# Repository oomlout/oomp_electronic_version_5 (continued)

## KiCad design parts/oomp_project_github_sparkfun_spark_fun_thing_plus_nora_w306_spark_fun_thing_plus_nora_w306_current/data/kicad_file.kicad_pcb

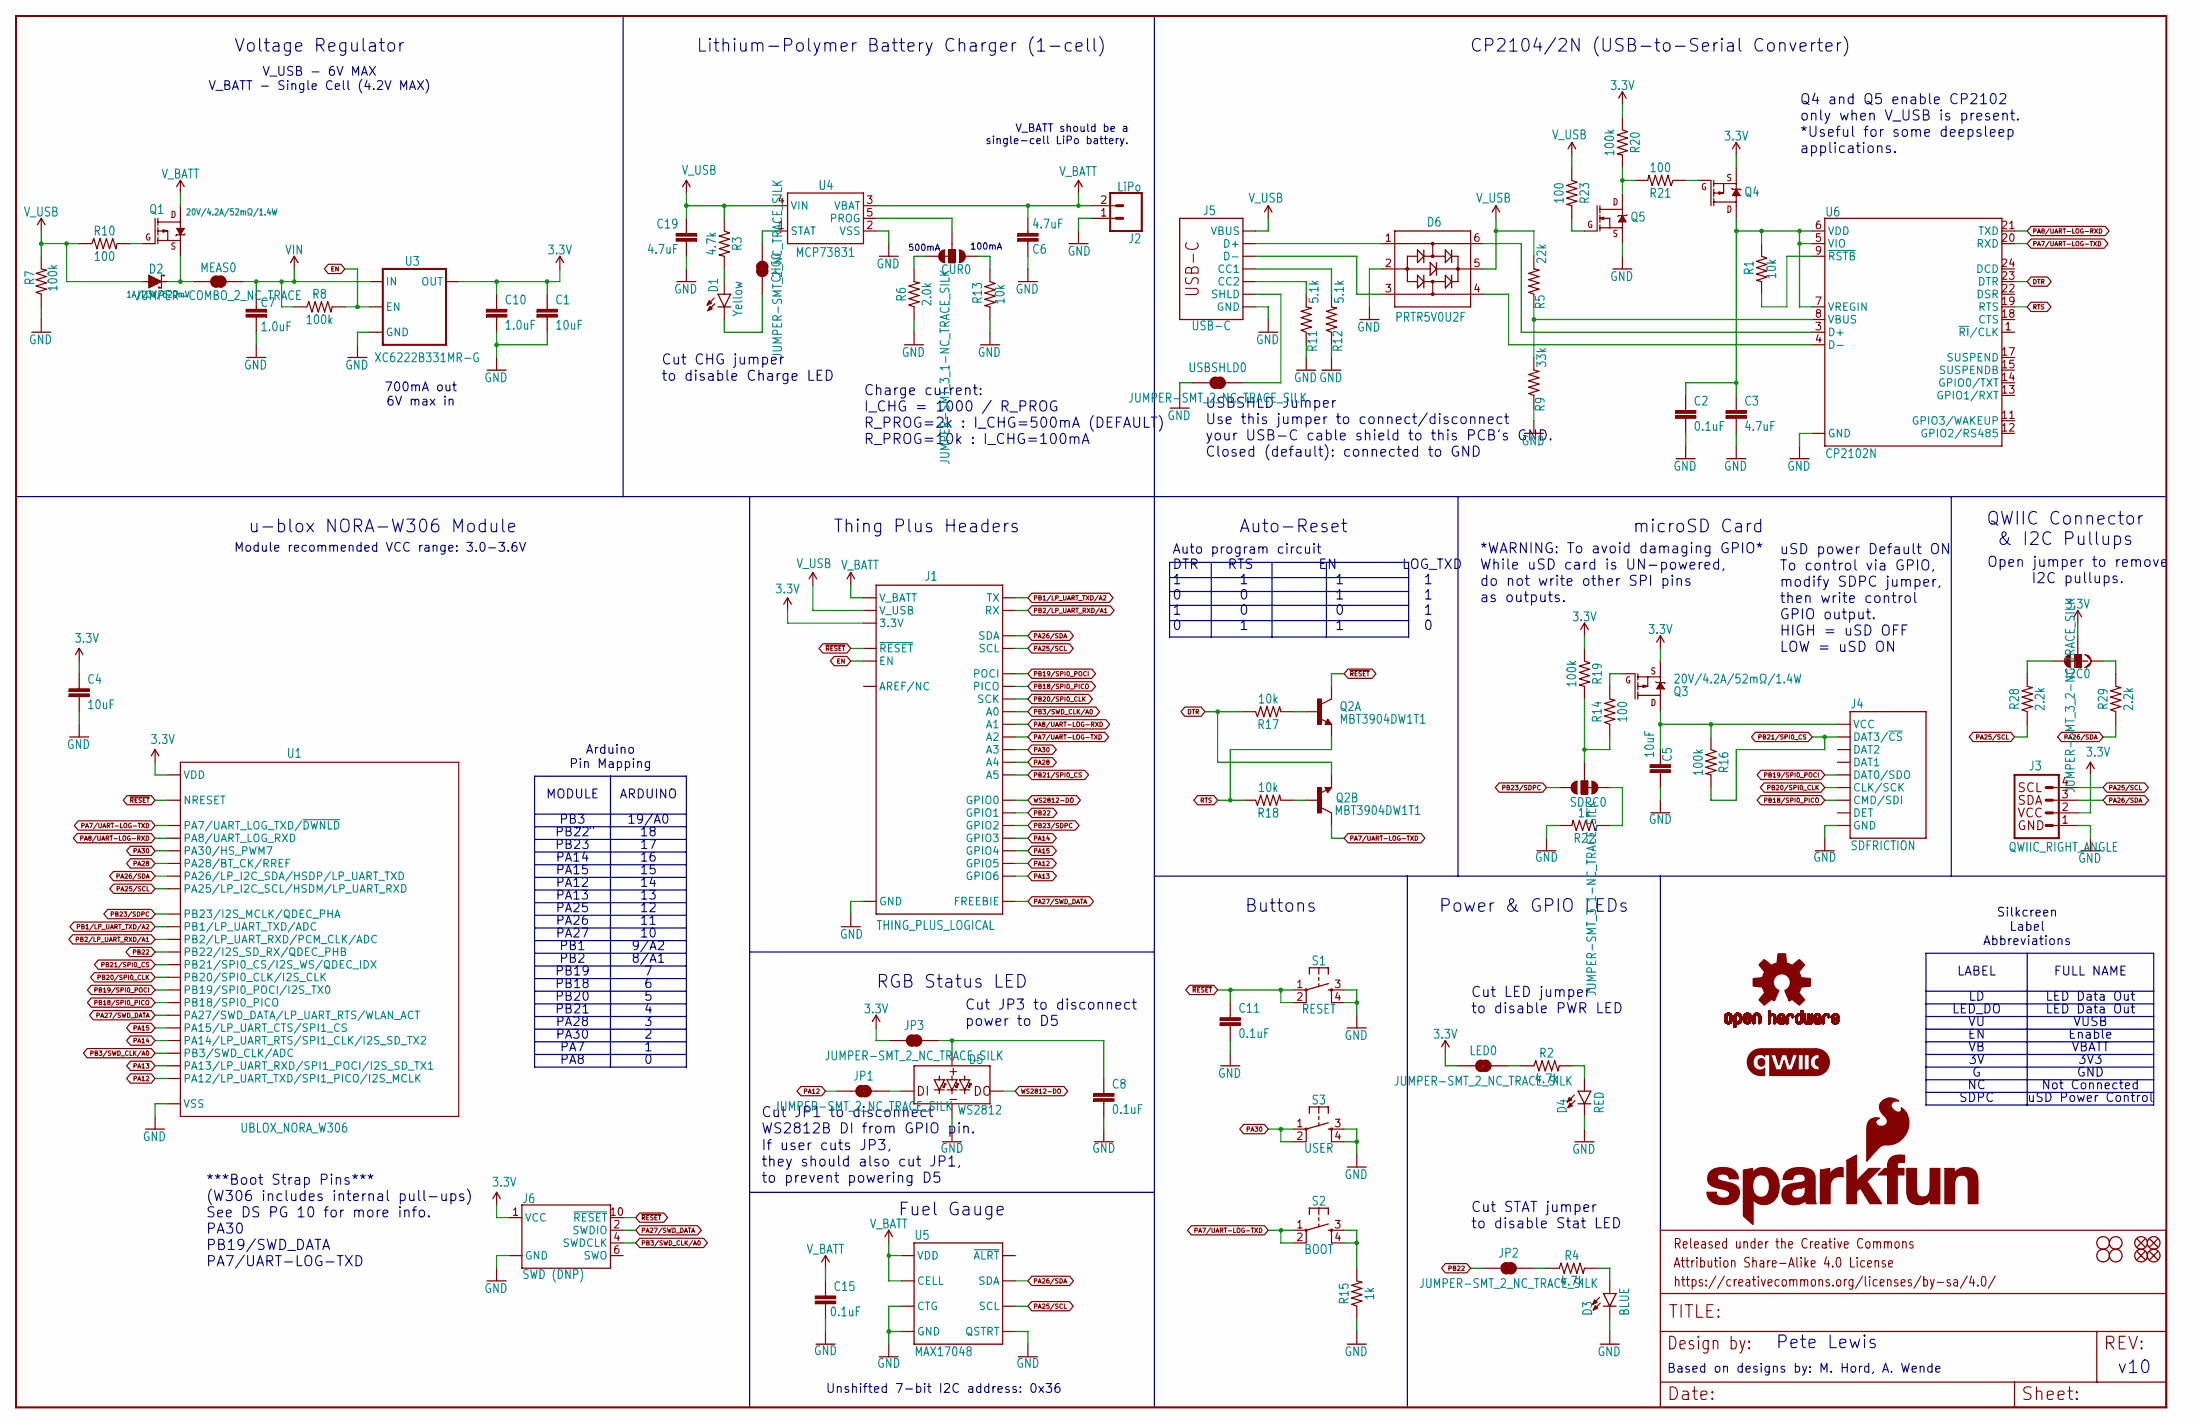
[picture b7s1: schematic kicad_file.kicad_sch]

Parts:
C1, C4, C5: 10uF; 0402-TIGHT
C2, C8, C11, C15: 0.1uF; 0402-TIGHT
C3, C6, C19: 4.7uF; 0603
C7, C10: 1.0uF; 0402-TIGHT
CHG0: JUMPER-SMT_2_NC_TRACE_SILK; SMT-JUMPER_2_NC_TRACE_SILK
CUR0: JUMPER-SMT_3_1-NC_TRACE_SILK; SMT-JUMPER_3_1-NC_TRACE_SILK
D1: Yellow; LED-0603
D2: 1A/23V/620mV; SOD-323
D3: BLUE; LED-0603
D4: RED; LED-0603
D5: WS2812; WS2812-2020
D6: PRTR5V0U2F; SOT886
FD1, FD2, FD3, FD4: FIDUCIALUFIDUCIAL; FIDUCIAL-MICRO
FRAME1: FRAME-LEDGER; CREATIVE_COMMONS
H1, H2, H3, H4: STAND-OFF
I2C0: JUMPER-SMT_3_2-NC_TRACE_SILK; SMT-JUMPER_3_2-NC_TRACE_SILK
J1: THING_PLUS_LOGICAL; THING_PLUS
J2: LiPo; JST-2-SMD
J3: QWIIC_RIGHT_ANGLE; JST04_1MM_RA
J4: SDFRICTION; MICROSD_TINY
J5: USB-C; USB-C-16P-4LAYER-ISOLATED
J6: SWD (DNP); 2X5-SMD-UNSHROUDED_DNP_NO_PASTE
JP1, JP2, JP3: JUMPER-SMT_2_NC_TRACE_SILK; SMT-JUMPER_2_NC_TRACE_SILK
LED0: JUMPER-SMT_2_NC_TRACE_SILK; SMT-JUMPER_2_NC_TRACE_SILK
LOGO2: OSHW-LOGOM; OSHW-LOGO-M
LOGO3: SFE_LOGO_NAME_FLAME.1_INCH; SFE_LOGO_NAME_FLAME_.1
LOGO6: QWIIC_LOGO_4MM; QWIIC_4MM
MEAS0: JUMPER-COMBO_2_NC_TRACE; COMBO-JUMPER_2_NC_TRACE
Q1, Q3, Q4: 20V/4.2A/52mΩ/1.4W; SOT23-3
Q2: MBT3904DW1T1; SC70-6
Q5: 20V/0.2A/8MHz/1.2Ω/1Vth; SOT-416FL
R1, R13, R17, R18: 10k; 0402-TIGHT
R2, R3, R4: 4.7k; 0402-TIGHT
R5: 22k; 0402-TIGHT
R6: 2.0k; 0603
R7, R8, R16, R19, R20: 100k; 0402-TIGHT
R9: 33k; 0402-TIGHT
R10, R14, R21, R23: 100; 0402-TIGHT
R11, R12: 5.1k; 0402-TIGHT
R15, R22: 1k; 0402-TIGHT
R28, R29: 2.2k; 0402-TIGHT
S1: RESET; TACTILE_SWITCH_SMD_4.6X2.8MM
S2: BOOT; TACTILE_SWITCH_SMD_4.6X2.8MM
S3: USER; TACTILE_SWITCH_SMD_4.6X2.8MM
SDPC0: JUMPER-SMT_3_1-NC_TRACE_SILK; SMT-JUMPER_3_1-NC_TRACE_SILK
U1: UBLOX_NORA_W306; UBLOX-NORA-W3
U3: XC6222B331MR-G; SOT23-5
U4: MCP73831; SOT23-5
U5: MAX17048; DFN-8
U6: CP2102N; QFN24
USBSHLD0: JUMPER-SMT_2_NC_TRACE_SILK; SMT-JUMPER_2_NC_TRACE_SILK

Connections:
3.3V: C1.1, C4.1, C10.1, I2C0.2, J1.27 (3.3V), J3.2, J6.1 (VCC), JP3.1, LED0.1, Q3.2 (S), Q4.2 (S), R19.1, R20.1, U1.A7 (VDD), U1.A8 (VDD), U1.B7 (VDD), U3.5 (OUT)
CC1: J5.A5 (CC1), R12.2
CC2: J5.B5 (CC2), R11.2
CHG: CHG0.2, U4.1 (STAT)
DTR: Q2.1 (E), R17.1, U6.23 (DTR)
EN: J1.11 (EN), R8.2, U3.3 (EN)
GND: C1.2, C2.2, C3.2, C4.2, C5.2, C6.2, C7.2, C8.2, C10.2, C11.2, C15.2, C19.2, D3.C, D4.C, D5.GND, D6.2, J1.25 (GND), J2.1 (2), J3.1, J4.6 (GND), J4.GND1 (GND), J4.GND2 (GND), J4.GND3 (GND), J4.GND4 (GND), J4.GND5 (GND), J4.GND6 (GND), J5.GND, J5.GND2 (GND), J6.3 (GND), J6.5 (GND), J6.9 (GND), Q5.2 (S), R6.1, R7.1, R9.1, R11.1, R12.1, R13.2, R15.1, R22.2, S1.3, S1.4, S3.3, S3.4, U1.A1 (VSS), U1.A9 (VSS), U1.B2 (VSS), U1.B8 (VSS), U1.E4 (VSS), U1.E5 (VSS), U1.F4 (VSS), U1.F5 (VSS), U1.K2 (VSS), U1.K3 (VSS), U1.K5 (VSS), U1.K7 (VSS), U1.K8 (VSS), U1.L1 (VSS), U1.L9 (VSS), U1.M1 (VSS), U1.M2 (VSS), U1.M8 (VSS), U1.M9 (VSS), U3.2 (GND), U4.2 (VSS), U5.1 (CTG), U5.4 (GND), U5.6 (QSTRT), U5.9 (GND), U6.2 (GND), U6.PAD (GND), USBSHLD0.1
unnamed: R1.2, U6.9 (~RSTB)
unnamed: D3.A, R4.2
unnamed: Q2.5 (B), R17.2
unnamed: R5.1, R9.2, U6.8 (VBUS)
unnamed: Q2.2 (B), R18.2
unnamed: CHG0.1, D1.C
unnamed: Q1.1 (G), R10.2
unnamed: R15.2, S2.3, S2.4
unnamed: CUR0.2, U4.5 (PROG)
unnamed: D5.DI, JP1.2
unnamed: CUR0.1, R13.1
unnamed: LED0.2, R2.1
unnamed: CUR0.3, R6.2
unnamed: D4.A, R2.2
unnamed: D6.6, U6.3 (D+)
unnamed: D6.1, J5.A6 (D+), J5.B6 (D+)
unnamed: D1.A, R3.2
unnamed: D6.4, U6.4 (D-)
unnamed: D6.3, J5.A7 (D-), J5.B7 (D-)
unnamed: I2C0.3, R28.2
unnamed: I2C0.1, R29.2
unnamed: JP2.2, R4.1
unnamed: D2.C, MEAS0.1, MEAS0.3 (1), Q1.2 (S)
unnamed: Q3.1 (G), R14.2
unnamed: C5.1, J4.4 (VCC), Q3.3 (D), R16.1
unnamed: R14.1, R19.2, SDPC0.2
unnamed: Q5.3 (D), R20.2, R21.2
unnamed: C8.1, D5.VCC, JP3.2
unnamed: C2.1, C3.1, Q4.3 (D), R1.1, U6.5 (VIO), U6.6 (VDD), U6.7 (VREGIN)
unnamed: Q4.1 (G), R21.1
unnamed: Q5.1 (G), R23.2
unnamed: R22.1, SDPC0.3
PA7/UART-LOG-TXD: J1.22 (A2), Q2.6 (C), S2.1, S2.2, U1.A5 (PA7/UART_LOG_TXD/~DWNLD), U6.20 (RXD)
PA8/UART-LOG-RXD: J1.23 (A1), U1.A6 (PA8/UART_LOG_RXD), U6.21 (TXD)
PA12: J1.4 (GPIO5), JP1.1, U1.J9 (PA12/LP_UART_TXD/SPI1_PICO/I2S_MCLK)
PA13: J1.3 (GPIO6), U1.J8 (PA13/LP_UART_RXD/SPI1_POCI/I2S_SD_TX1)
PA14: J1.6 (GPIO3), U1.H9 (PA14/LP_UART_RTS/SPI1_CLK/I2S_SD_TX2)
PA15: J1.5 (GPIO4), U1.H8 (PA15/LP_UART_CTS/SPI1_CS)
PA25/SCL: J1.2 (SCL), J3.4, R28.1, U1.C2 (PA25/LP_I2C_SCL/HSDM/LP_UART_RXD), U5.7 (SCL)
PA26/SDA: J1.1 (SDA), J3.3, R29.1, U1.C1 (PA26/LP_I2C_SDA/HSDP/LP_UART_TXD), U5.8 (SDA)
PA27/SWD_DATA: J1.13 (FREEBIE), J6.2 (SWDIO), U1.H2 (PA27/SWD_DATA/LP_UART_RTS/WLAN_ACT)
PA28: J1.20 (A4), U1.B3 (PA28/BT_CK/RREF)
PA30: J1.21 (A3), S3.1, S3.2, U1.B1 (PA30/HS_PWM7)
PB1/LP_UART_TXD/A2: J1.14 (TX), U1.D8 (PB1/LP_UART_TXD/ADC)
PB2/LP_UART_RXD/A1: J1.15 (RX), U1.E8 (PB2/LP_UART_RXD/PCM_CLK/ADC)
PB3/SWD_CLK/A0: J1.24 (A0), J6.4 (SWDCLK), U1.J2 (PB3/SWD_CLK/ADC)
PB18/SPI0_PICO: J1.17 (PICO), J4.3 (CMD/SDI), U1.G9 (PB18/SPI0_PICO)
PB19/SPI0_POCI: J1.16 (POCI), J4.7 (DAT0/SDO), U1.G8 (PB19/SPI0_POCI/I2S_TX0)
PB20/SPI0_CLK: J1.18 (SCK), J4.5 (CLK/SCK), U1.F9 (PB20/SPI0_CLK/I2S_CLK)
PB21/SPI0_CS: J1.19 (A5), J4.2 (DAT3/~CS), R16.2, U1.F8 (PB21/SPI0_CS/I2S_WS/QDEC_IDX)
PB22: J1.8 (GPIO1), JP2.1, U1.E9 (PB22/I2S_SD_RX/QDEC_PHB)
PB23/SDPC: J1.7 (GPIO2), SDPC0.1, U1.C8 (PB23/I2S_MCLK/QDEC_PHA)
RTS: Q2.4 (E), R18.1, U6.19 (RTS)
USB_SHLD: J5.SHLD1 (SHLD), J5.SHLD2 (SHLD), J5.SHLD3 (SHLD), J5.SHLD4 (SHLD), J5.SHLD5 (SHLD), J5.SHLD6 (SHLD), J5.SHLD7 (SHLD), J5.SHLD8 (SHLD), USBSHLD0.2
VIN: C7.1, MEAS0.2, MEAS0.4 (2), R8.1, U3.1 (IN)
V_BATT: C6.1, C15.1, J1.12 (V_BATT), J2.2 (1), Q1.3 (D), U4.3 (VBAT), U5.2 (CELL), U5.3 (VDD)
V_USB: C19.1, D2.A, D6.5, J1.10 (V_USB), J5.VBUS1 (VBUS), J5.VBUS2 (VBUS), R3.1, R5.2, R7.2, R10.1, R23.1, U4.4 (VIN)
WS2812-DO: D5.DO, J1.9 (GPIO0)
~RESET: C11.1, J1.28 (~RESET), J6.10 (~RESET), Q2.3 (C), S1.1, S1.2, U1.J3 (NRESET)

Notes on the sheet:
Lithium-Polymer Battery Charger (1-cell)
Cut JP3 to disconnect power to D5
PA26
PA15
u-blox NORA-W306 Module
" "
V_BATT should be a single-cell LiPo battery.
PB2
700mA out 6V max in
LED Data Out
microSD Card
PA8
500mA
uSD power Default ON To control via GPIO, modify SDPC jumper, then write control GPIO output. HIGH = uSD OFF LOW = uSD ON
PB20
Auto-Reset
PB22
Based on designs by: M. Hord, A. Wende
PB21
Silkcreen Label Abbreviations
Auto program circuit DTR RTS EN LOG_TXD 1 1 1 1 0 0 1 1 1 0 0 1 0 1 1 0
ARDUINO
SDPC
PA28
V_USB - 6V MAX V_BATT - Single Cell (4.2V MAX)
Arduino Pin Mapping
FULL NAME
***Boot Strap Pins*** (W306 includes internal pull-ups) See DS PG 10 for more info. PA30 PB19/SWD_DATA PA7/UART-LOG-TXD
PB18
Fuel Gauge
PB23
PB1
Cut LED jumper to disable PWR LED
Power & GPIO LEDs
9/A2
PA12
PA13
PA25
Charge current: I_CHG = 1000 / R_PROG R_PROG=2k : I_CHG=500mA (DEFAULT) R_PROG=10k : I_CHG=100mA
v10

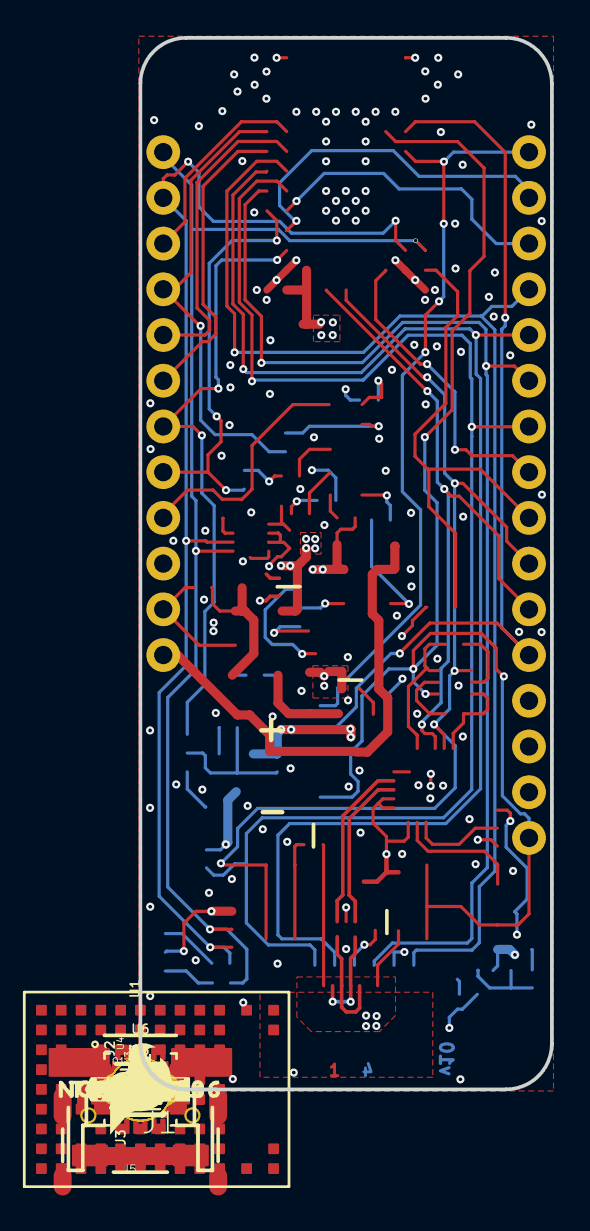
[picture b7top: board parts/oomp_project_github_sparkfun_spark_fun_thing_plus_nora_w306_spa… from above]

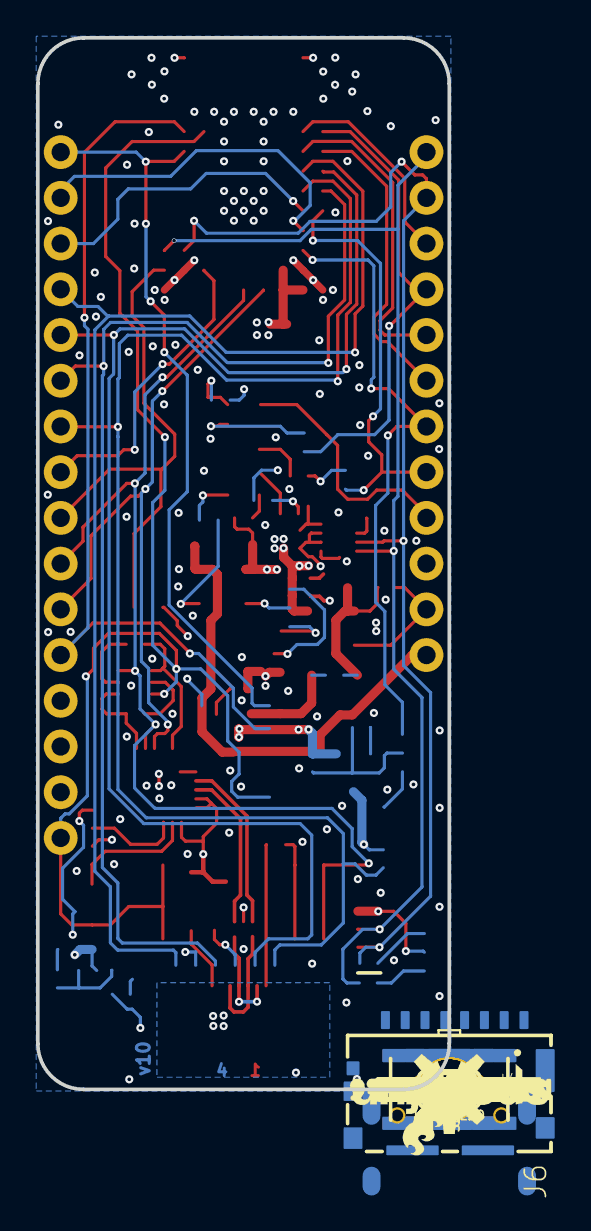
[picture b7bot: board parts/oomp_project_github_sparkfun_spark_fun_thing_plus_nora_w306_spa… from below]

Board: 4 copper layers, 22.9 x 58.4 mm, 170 parts (74 on the bottom side), 66 nets.

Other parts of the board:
U$1, U$22: #17#11
U$2: BOOT0
U$3: #MEAS#1714141838
U$4: IO180
U$5: NORA#W3060
U$6: ##RST##23061714141845
U$7: USER0
U$8: SFE_LOGO_FLAME_.2
U$9: IO20
U$10: #GND#ON#3061714141842
U$11: #SDPC#0
U$12: #A0#1
U$13: #SDA#11#28
U$14: #17#28
U$15: #0#4
U$16: #1#4
U$17: #SCL#12#28
U$18: #18#28
U$19: SFE_LOGO_FLAME_.1
U$20: #LD#29
U$21: RGB_IO140
U$23: PWR0
U$24: #CUR#0
U$25: THING_PLUS1714141839
U$26, U$77: #VB26
U$28: NORA#W3061714141840
U$30: #13#13
U$31: #14#14
U$32: #15#15
U$33: #16#16
U$35: #18#18
U$36: #11#91420
U$37: #12#91420
U$38: #13#91420
U$39: #14#91420
U$40: #15#91420
U$41: #VUSB#0
U$42: #JP3#23061714141846
U$43: #EN#0
U$44: #16#91420
U$45: #3V3#0
U$46: #NC#2
U$47: #A0#18
U$48: #8#91421
U$49: #7#8
U$50: #6#8
U$51: #5#8
U$52: #4#8
U$53: #3#8
U$54: #2#8
U$55: #1#8
U$56: #0#8
U$57: #3V#23
U$58: #JP2#0
U$59: ORDERING_INSTRUCTIONS
U$60: #SWD#501
U$61: #100#23061714141846
U$62: THING_PLUS_0
U$63: #SHLD#9
U$64: #GND#10
U$65: #JP1#0
U$66: #PWR#14
U$67: #CHG#13
U$68: ##RESET##19
U$69: #NC#21
U$70: #9#10
U$71: #LED_DO#0
U$72: #I2C#3
U$73: #500#23061714141846
U$74: #10#11
U$75: #G#22
U$76: #VU#23
U$78: CHG0
U$79: RESET0
U$80: #EN#27
U$81: #2#28
U$82: #3#28
U$83: #4#CS#28
U$84: #5#SCK#28
U$85: #6#PICO#28
U$86: #7#POCI#28
U$87: #9#TX1#A2#28
U$88: #8#RX1#A1#28
U$91: #10#28

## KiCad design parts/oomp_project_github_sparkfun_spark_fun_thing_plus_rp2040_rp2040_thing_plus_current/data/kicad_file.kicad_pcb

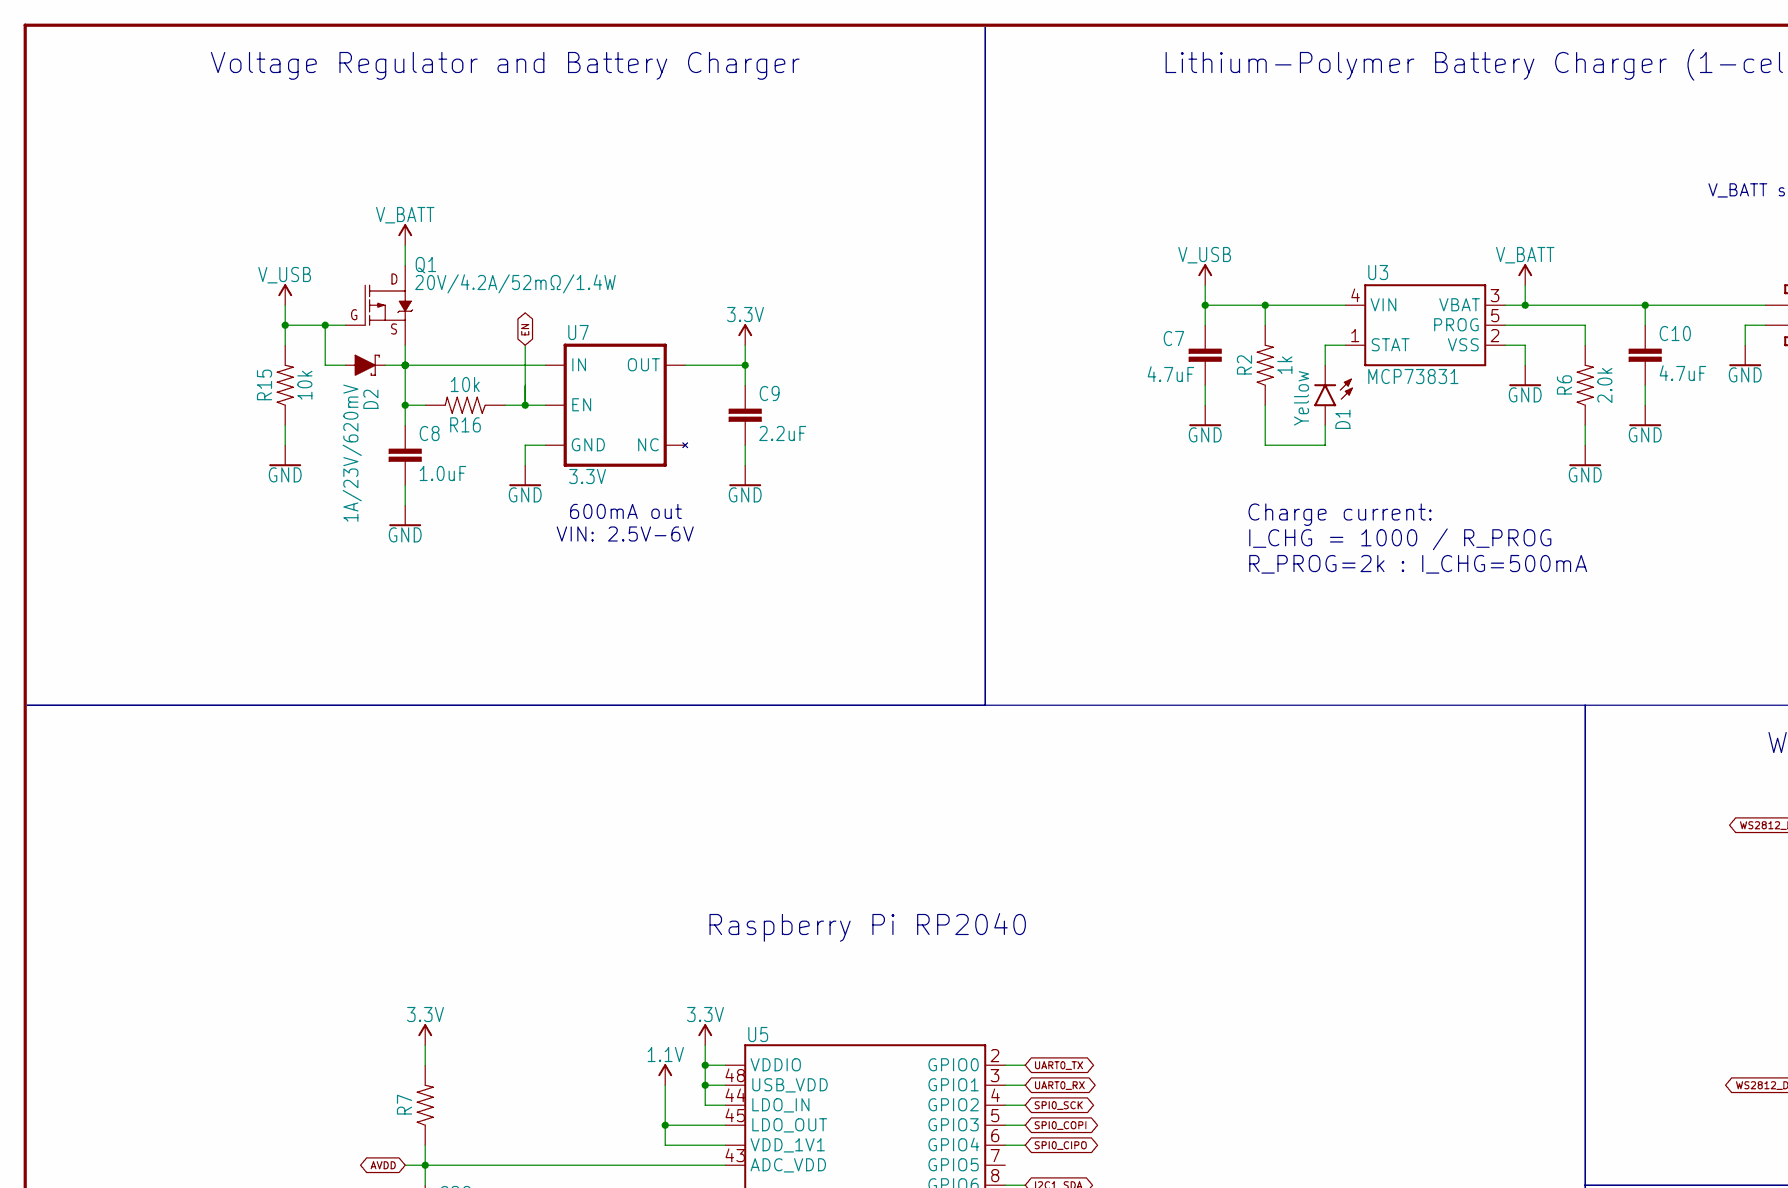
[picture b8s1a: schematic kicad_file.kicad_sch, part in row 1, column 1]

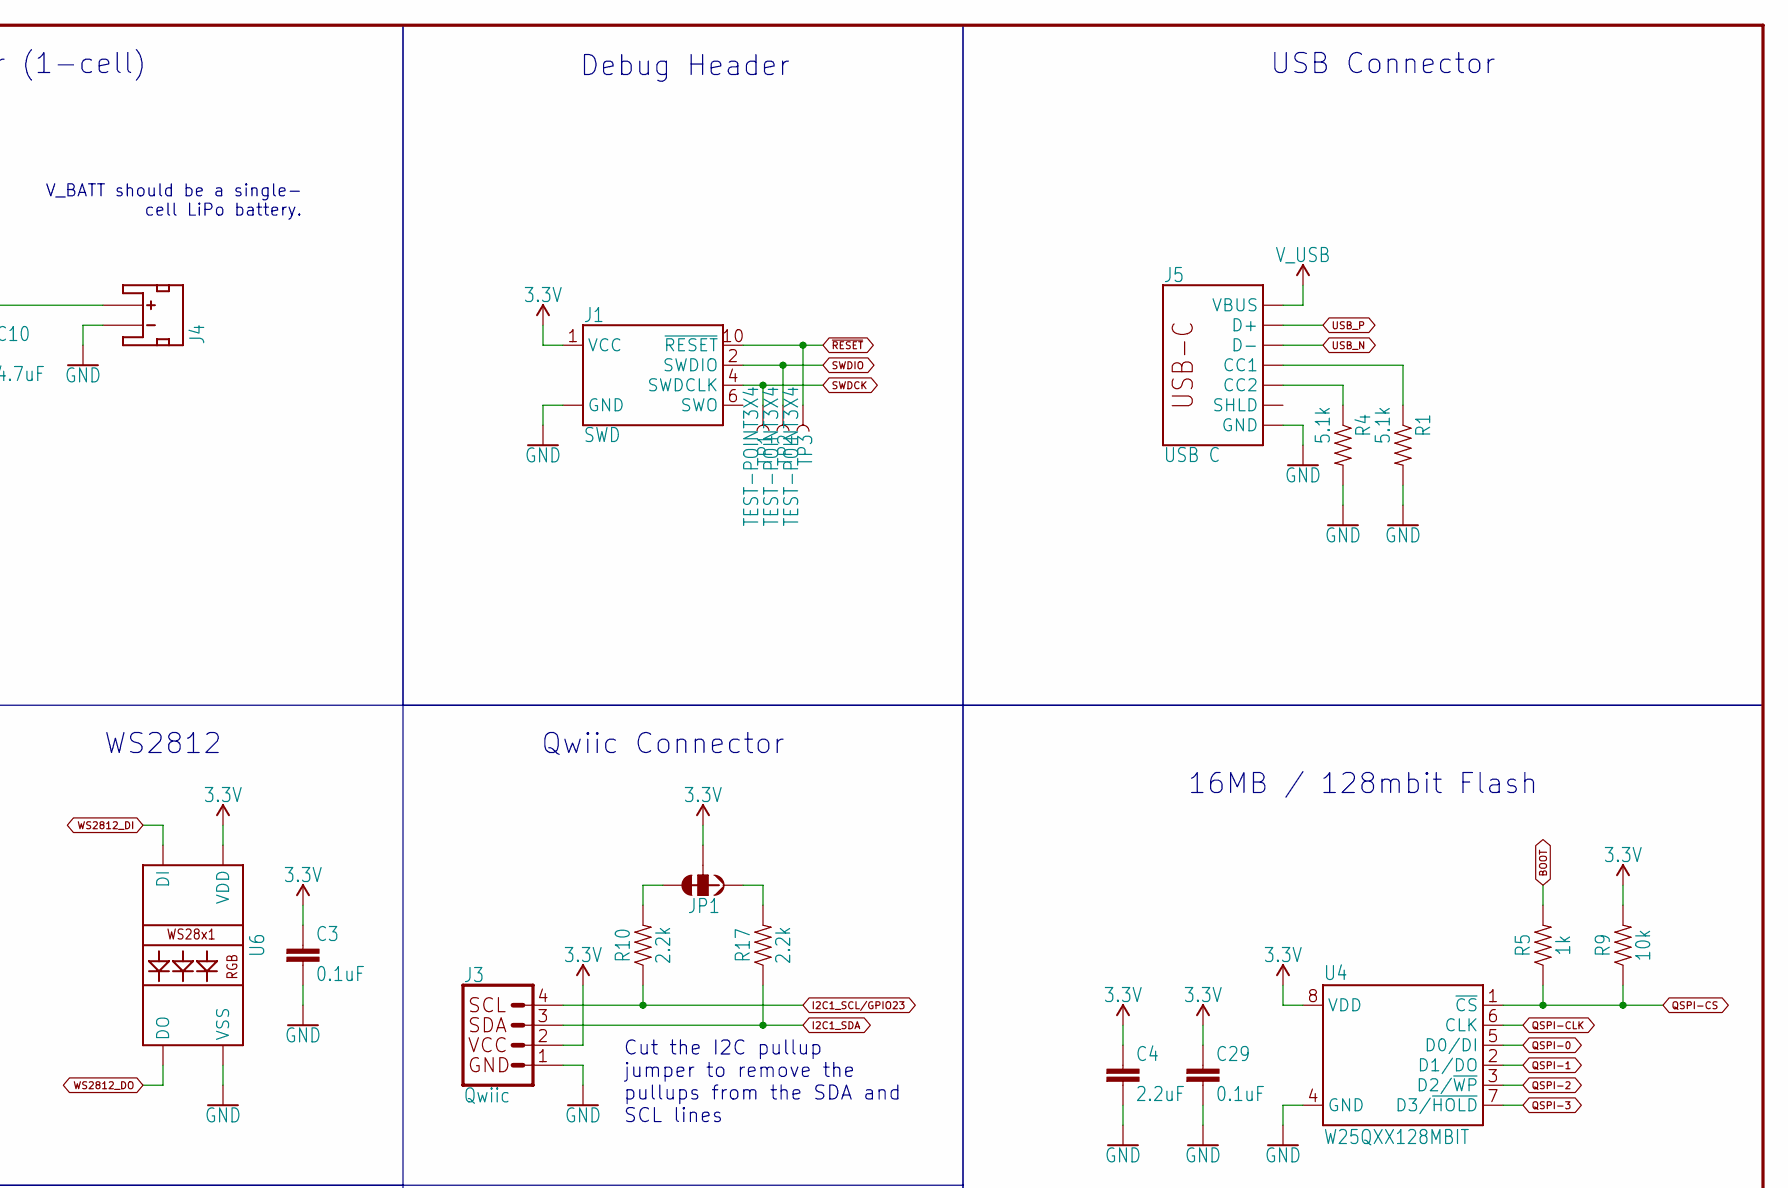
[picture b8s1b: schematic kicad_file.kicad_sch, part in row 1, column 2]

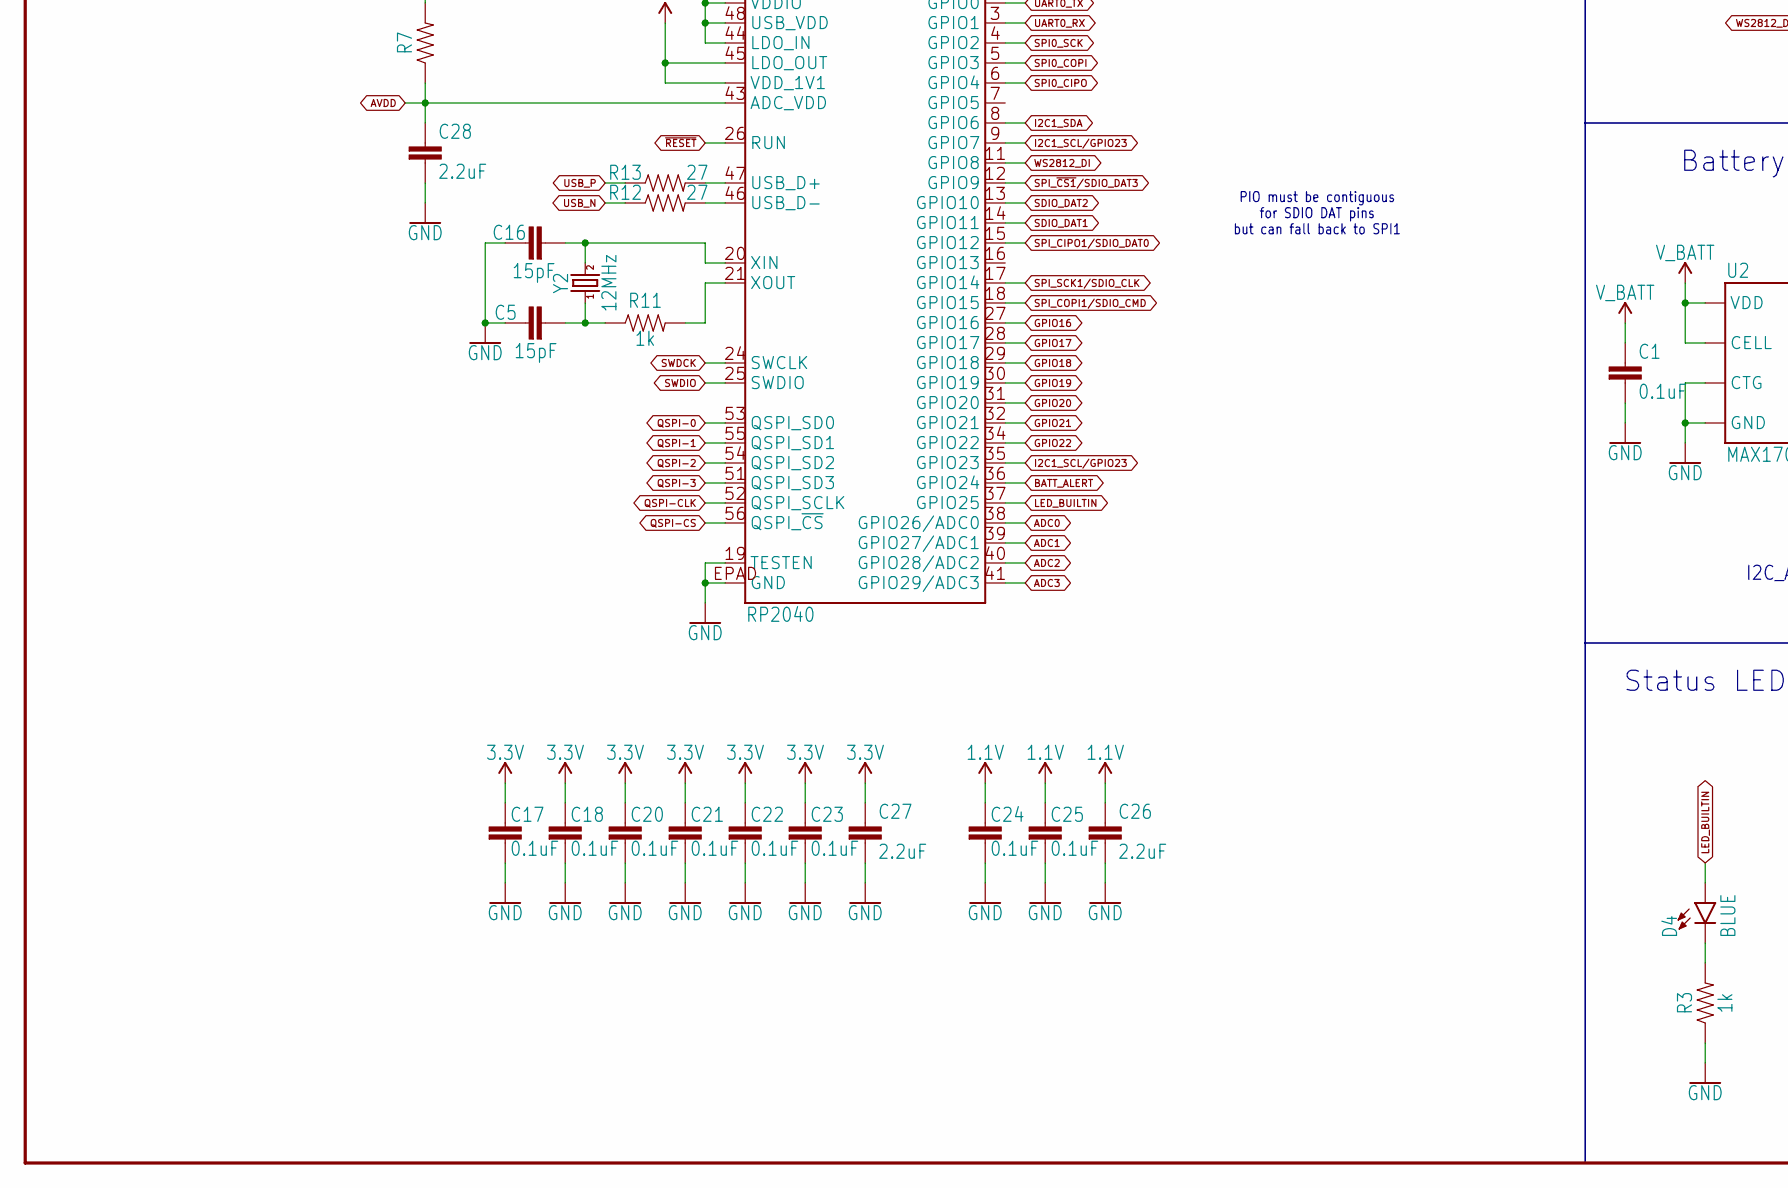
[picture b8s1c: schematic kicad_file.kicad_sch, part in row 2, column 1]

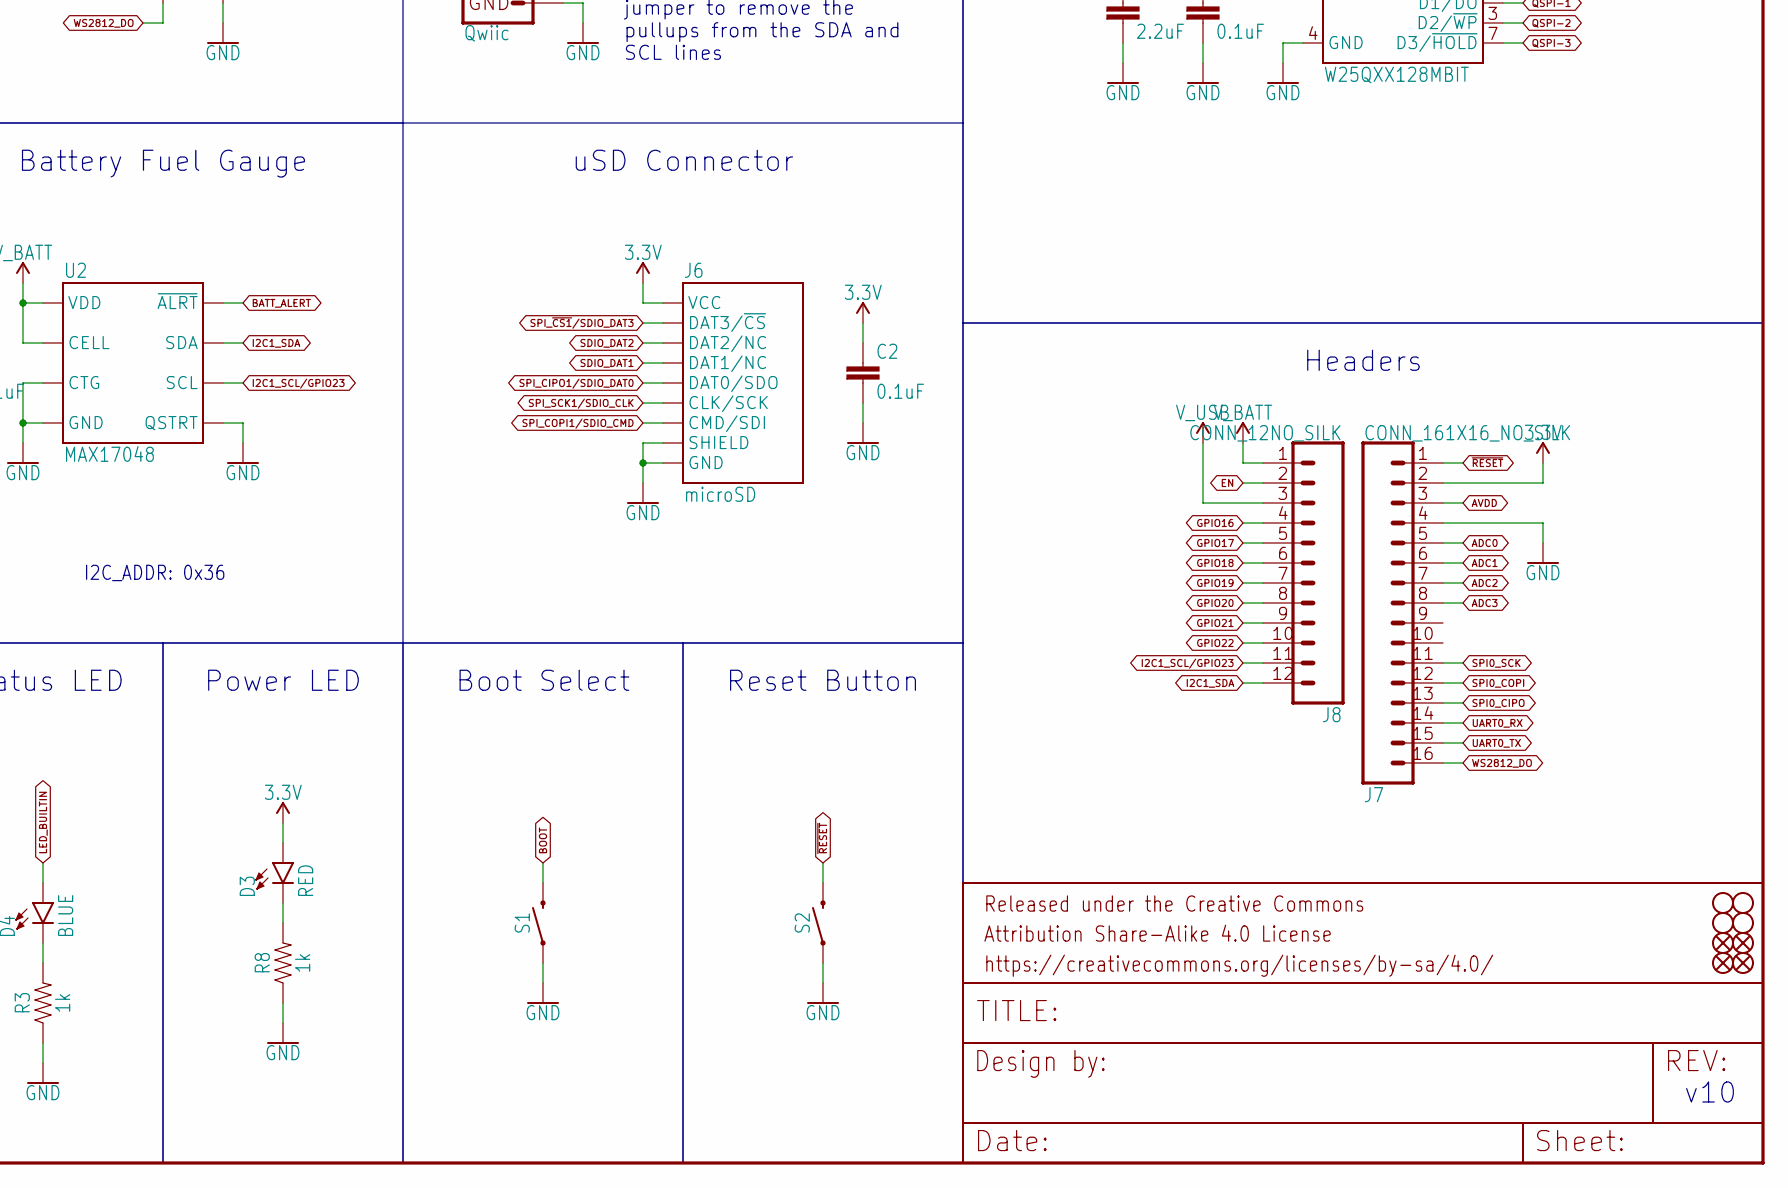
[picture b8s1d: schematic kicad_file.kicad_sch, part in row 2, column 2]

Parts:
C1, C2, C3, C17, C18, C20, C21, C22, C23, C24, C25, C29: 0.1uF; 0402-TIGHT
C4, C9, C26, C27, C28: 2.2uF; 0402-TIGHT
C5, C16: 15pF; 0402-TIGHT
C7, C10: 4.7uF; 0402-TIGHT
C8: 1.0uF; 0402-TIGHT
D1: Yellow; LED-0603
D2: 1A/23V/620mV; SOD-323
D3: RED; LED-0603
D4: BLUE; LED-0603
FD1, FD2, FD3, FD4: FIDUCIALUFIDUCIAL; FIDUCIAL-MICRO
FRAME1: FRAME-LEDGER; CREATIVE_COMMONS
H1, H2, H3, H4: STAND-OFF
J1: SWD; 2X5-PTH-1.27MM
J3: Qwiic; JST04_1MM_RA
J4: JST_2MM_MALE; JST-2-SMD
J5: USB C; USB-C-16P-4LAYER-ISOLATED
J6: microSD; MICRO-SD-SOCKET
J7: CONN_161X16_NO_SILK; 1X16_NO_SILK
J8: CONN_12NO_SILK; 1X12_NO_SILK
JP1: JUMPER-SMT_3_2-NC_TRACE_SILK; SMT-JUMPER_3_2-NC_TRACE_SILK
Q1: 20V/4.2A/52mΩ/1.4W; SOT23-3
R1, R4: 5.1k; 0402-TIGHT
R2, R3, R5, R8, R11: 1k; 0402-TIGHT
R6: 2.0k; 0603
R7: 200OHM-0402T-1/16W-1%; 0402-TIGHT
R9, R15, R16: 10k; 0402-TIGHT
R10, R17: 2.2k; 0402-TIGHT
R12, R13: 27; 0402-TIGHT
S1, S2: MOMENTARY-SWITCH-SPST-SMD-5.2MM-TALL; TACTILE_SWITCH_SMD_5.2MM
TP1, TP2, TP3: TEST-POINT3X4; PAD.03X.04
U2: MAX17048; DFN-8
U3: MCP73831; SOT23-5
U4: W25QXX128MBIT; WSON-8-6X5-SKINNY_CENTERPAD
U5: RP2040; QFN-56
U6: WS2812-2020
U7: 3.3V; SOT23-5
Y2: 12MHz; CRYSTAL-SMD-2X2.5MM

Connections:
1.1V: C24.1, C25.1, C26.1, U5.23 (VDD_1V1), U5.45 (LDO_OUT), U5.50 (VDD_1V1)
3.3V: C2.1, C3.1, C4.1, C9.1, C17.1, C18.1, C20.1, C21.1, C22.1, C23.1, C27.1, C29.1, D3.A, J1.1 (VCC), J3.2, J6.VCC, J7.2, JP1.2, R7.2, R9.2, U4.8 (VDD), U5.1 (VDDIO), U5.10 (VDDIO), U5.22 (VDDIO), U5.33 (VDDIO), U5.42 (VDDIO), U5.44 (LDO_IN), U5.48 (USB_VDD), U5.49 (VDDIO), U6.4 (VDD), U7.5 (OUT)
ADC0: J7.5, U5.38 (GPIO26/ADC0)
ADC1: J7.6, U5.39 (GPIO27/ADC1)
ADC2: J7.7, U5.40 (GPIO28/ADC2)
ADC3: J7.8, U5.41 (GPIO29/ADC3)
AVDD: C28.1, J7.3, R7.1, U5.43 (ADC_VDD)
BATT_ALERT: U2.5 (~ALRT), U5.36 (GPIO24)
BOOT: R5.2, S1.3 (2)
EN: J8.2, R16.1, U7.3 (EN)
GND: C1.2, C2.2, C3.2, C4.2, C5.1, C7.2, C8.2, C9.2, C10.2, C16.1, C17.2, C18.2, C20.2, C21.2, C22.2, C23.2, C24.2, C25.2, C26.2, C27.2, C28.2, C29.2, J1.3 (GND), J1.5 (GND), J1.9 (GND), J3.1, J4.1 (-), J5.GND, J5.GND2 (GND), J6.CD1 (SHIELD), J6.GND, J6.GND1 (GND), J6.GND3 (GND), J7.4, R1.2, R3.1, R4.2, R6.1, R8.1, R15.1, S1.1, S2.1, U2.1 (CTG), U2.4 (GND), U2.6 (QSTRT), U2.9 (GND), U3.2 (VSS), U4.4 (GND), U5.19 (TESTEN), U5.EPAD (GND), U6.2 (VSS), U7.2 (GND)
GPIO16: J8.4, U5.27 (GPIO16)
GPIO17: J8.5, U5.28 (GPIO17)
GPIO18: J8.6, U5.29 (GPIO18)
GPIO19: J8.7, U5.30 (GPIO19)
GPIO20: J8.8, U5.31 (GPIO20)
GPIO21: J8.9, U5.32 (GPIO21)
GPIO22: J8.10, U5.34 (GPIO22)
I2C1_SCL/GPIO23: J3.4, J8.11, R10.1, U2.7 (SCL), U5.9 (GPIO7), U5.35 (GPIO23)
I2C1_SDA: J3.3, J8.12, R17.1, U2.8 (SDA), U5.8 (GPIO6)
LED_BUILTIN: D4.A, U5.37 (GPIO25)
unnamed: D4.C, R3.2
unnamed: JP1.3, R10.2
unnamed: JP1.1, R17.2
unnamed: R11.2, U5.21 (XOUT)
unnamed: C16.2, U5.20 (XIN), Y2.P3 (2)
unnamed: C5.2, R11.1, Y2.P1 (1)
unnamed: D3.C, R8.2
unnamed: D1.C, U3.1 (STAT)
unnamed: J5.A5 (CC1), R1.1
unnamed: J5.B5 (CC2), R4.1
unnamed: R6.2, U3.5 (PROG)
unnamed: C8.1, D2.C, Q1.2 (S), R16.2, U7.1 (IN)
unnamed: D1.A, R2.1
QSPI-0: U4.5 (D0/DI), U5.53 (QSPI_SD0)
QSPI-1: U4.2 (D1/DO), U5.55 (QSPI_SD1)
QSPI-2: U4.3 (D2/~WP), U5.54 (QSPI_SD2)
QSPI-3: U4.7 (D3/~HOLD), U5.51 (QSPI_SD3)
QSPI-CLK: U4.6 (CLK), U5.52 (QSPI_SCLK)
QSPI-CS: R5.1, R9.1, U4.1 (~CS), U5.56 (QSPI_~CS)
SDIO_DAT1: J6.DAT1 (DAT1/NC), U5.14 (GPIO11)
SDIO_DAT2: J6.DAT2 (DAT2/NC), U5.13 (GPIO10)
SPI0_CIPO: J7.13, U5.6 (GPIO4)
SPI0_COPI: J7.12, U5.5 (GPIO3)
SPI0_SCK: J7.11, U5.4 (GPIO2)
SPI_CIPO1/SDIO_DAT0: J6.DO/DAT0 (DAT0/SDO), U5.15 (GPIO12)
SPI_COPI1/SDIO_CMD: J6.DI/CMD (CMD/SDI), U5.18 (GPIO15)
SPI_SCK1/SDIO_CLK: J6.SCLK (CLK/SCK), U5.17 (GPIO14)
SPI_~CS1/SDIO_DAT3: J6.CS/DAT3 (DAT3/~CS), U5.12 (GPIO9)
SWDCK: J1.4 (SWDCLK), TP1.P$1, U5.24 (SWCLK)
SWDIO: J1.2 (SWDIO), TP2.P$1, U5.25 (SWDIO)
UART0_RX: J7.14, U5.3 (GPIO1)
UART0_TX: J7.15, U5.2 (GPIO0)
USB_F_N: R12.2, U5.46 (USB_D-)
USB_F_P: R13.2, U5.47 (USB_D+)
USB_N: J5.A7 (D-), J5.B7 (D-), R12.1
USB_P: J5.A6 (D+), J5.B6 (D+), R13.1
V_BATT: C1.1, C10.1, J4.2 (+), J8.1, Q1.3 (D), U2.2 (CELL), U2.3 (VDD), U3.3 (VBAT)
V_USB: C7.1, D2.A, J5.VBUS1 (VBUS), J5.VBUS2 (VBUS), J8.3, Q1.1 (G), R2.2, R15.2, U3.4 (VIN)
WS2812_DI: U5.11 (GPIO8), U6.3 (DI)
WS2812_DO: J7.16, U6.1 (DO)
~RESET: J1.10 (~RESET), J7.1, S2.3 (2), TP3.P$1, U5.26 (RUN)

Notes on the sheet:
Power LED
Headers
uSD Connector
Lithium-Polymer Battery Charger (1-cell)
I2C_ADDR: 0x36
v10
Battery Fuel Gauge
Debug Header
Voltage Regulator and Battery Charger
600mA out VIN: 2.5V-6V
WS2812
Cut the I2C pullup jumper to remove the pullups from the SDA and SCL lines
Charge current: I_CHG = 1000 / R_PROG R_PROG=2k : I_CHG=500mA
Boot Select
16MB / 128mbit Flash
Qwiic Connector
Status LED
USB Connector
V_BATT should be a single- cell LiPo battery.
PIO must be contiguous for SDIO DAT pins but can fall back to SPI1
Reset Button
Raspberry Pi RP2040
